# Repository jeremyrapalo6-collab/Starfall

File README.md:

# Starfall

Starfall is my first hardware project. I wanted to make a macropad because it seemed cool, and I chose to use my favorite colors, black and purple, along with my group name, **LTC**. This was a cool but long project, and I learned a lot while making it.

## What it is

Starfall is a 9-key macropad with a rotary encoder and a small OLED display. I designed it around a Seeed Studio XIAO RP2040 and made a custom PCB and case for it.

The macropad has three modes:

- **Everyday** - shortcuts for normal computer use
- **Gaming** - keys for games
- **Coding** - shortcuts for VS Code and Python

The bottom-right key changes between the three modes, and the OLED shows which mode is active.

## Design

The Celestial case pairs a black shell with purple side trusses, stars, a crescent and a bold slanted LTC logo. It has a stepped OLED surround and a recessed USB-C opening. Keycap symbols are illustrative; the preview includes the printable Starfall star knob.

## Hardware

- Seeed Studio XIAO RP2040
- 9 MX-compatible switches
- 9 1N4148 diodes
- 0.91-inch SSD1306 I2C OLED
- EC11 rotary encoder
- Custom 2-layer PCB
- Custom 3D-printed case
- 9 keycaps
- M3 screws and heat-set inserts

## Firmware

The firmware uses **KMK / CircuitPython**.

The three layers are:

### Everyday
Copy, paste, cut, undo, redo, select all, screenshot, media play/pause, and mode change.

### Gaming
A set of gaming keys plus the mode-change key.

### Coding
VS Code shortcuts such as run, debug, format, comment, terminal, split editor, command palette, quick open, and mode change.

## PCB

### Schematic

### PCB layout

### Front 3D view

### Back 3D view

### Gerber check

## Case

The current case is **Starfall Celestial** (114.4 x 116 x 22.9 mm including side trusses).

- Black: `production/Top.STEP` and `production/Bottom.STEP`.
- Purple: `production/Middle_Purple.STEP` and `production/Purple_Inlays_Print_Layout.STEP` (one set of accents).
- Matching STL files are provided. `Purple_Inlays.STEP` is the same accents in assembled positions: do not print both accent files.
- [Fully assembled STEP](CAD/Starfall_Fully_Assembled.STEP) and [colored GLB](CAD/Starfall_Fully_Assembled_Colored.glb).
- [Design changes and physical fit checks](DESIGN_NOTES.md) and [assembly instructions](CAD/MECHANICAL_NOTES.md).

The L has been shifted 0.35 mm right. The taller bottom retains M3x16 screws with recessed insert seats. The PCB layout is unchanged. Print the switch/insert coupons and check your actual cable before a full case: CAD checks do not guarantee physical fit. All files in production are current. The case PNGs and older assembly filenames are synchronized to the latest Celestial case; PCB screenshots describe the unchanged PCB.

Automated CAD results: [mechanical](production/MECHANICAL_VALIDATION.json), [exports](production/EXPORT_VALIDATION.json), [structural intersections](production/STRUCTURAL_COLLISIONS.json).

### Current case views

These views are rendered from the current assembly. Keycaps and legends are illustrative accessories; the knob matches the printable files. See [asset descriptions](assets/SCREENSHOTS.md).

[Download the complete printer ZIP (case + knob + samples)](production/Starfall-Complete-Printer-Pack.zip).

### Printable Starfall encoder knob

[Download the knob print pack](production/knob/Starfall-Knob-Print-Pack.zip) or browse [individual STL/STEP files and instructions](production/knob/README.md).

Print `Knob_Black.stl` in black and `Knob_Star_Purple.stl` in purple. Test `Dshaft_sample_6p2mm.stl` on the actual encoder first. The 6.1 and 6.3 mm samples provide fit alternatives; change the knob bore if needed before printing. Modeled clearances pass, but physical shaft fit and push travel require testing. Full-case previews and assembled STEP/GLB files now include this printable star knob.

## Bill of Materials

| Item | Qty | Part / Specification | Notes |
| --- | ---: | --- | --- |
| Microcontroller | 1 | Seeed Studio XIAO RP2040 | Hackpad MCU |
| Mechanical switch | 9 | MX-compatible PCB-mount switch | 1u switches |
| Diode | 9 | 1N4148 DO-35 through-hole | One per key |
| Rotary encoder | 1 | EC11E, 20 mm D-shaft | Encoder input |
| OLED | 1 | 0.91 in 128x32 SSD1306 I2C | 4-pin module |
| Keycap | 9 | 1u MX keycaps | 9 total |
| Encoder knob | 1 | D-shaft knob sized for EC11E | Knob for encoder |
| M3 screw | 4 | M3 x 16 mm | Deeper bottom; checked head envelope is diameter 5.5 x height 3 mm |
| Heat-set insert | 4 | M3 x 5 x 4 mm insert | 4.7 x 4.1 mm pocket below a 5.8 mm installation well |
| PCB | 1 | Starfall 2-layer PCB, 84.89 x 96.94 mm | Gerbers in `production/` |
| Case: black | 1 set | `Top.STEP` + `Bottom.STEP` | 3D printed |
| Case: purple | 1 set | `Middle_Purple.STEP` + `Purple_Inlays.STEP` | 3D printed accents |

The full BOM with source/reference links is also available in [`BOM.csv`](BOM.csv).

## Files

- `PCB/` - KiCad schematic, PCB, and project files
- `CAD/` - case, assemblies, and full-color GLB preview
- `production/` - final STEP/STL case parts, Gerbers, print-ready check, and `main.py`
- `Firmware/` - KMK firmware source
- `assets/` - project screenshots and graphics
- `tools/` - reproducible final-case generator
- `BOM.csv` - bill of materials with reference links

## What I learned

This was my first project, so I learned a lot about KiCad, schematics, PCB routing, key matrices, diodes, 3D models, case design, Gerbers, and firmware. It took a while, but seeing the whole project come together was worth it.

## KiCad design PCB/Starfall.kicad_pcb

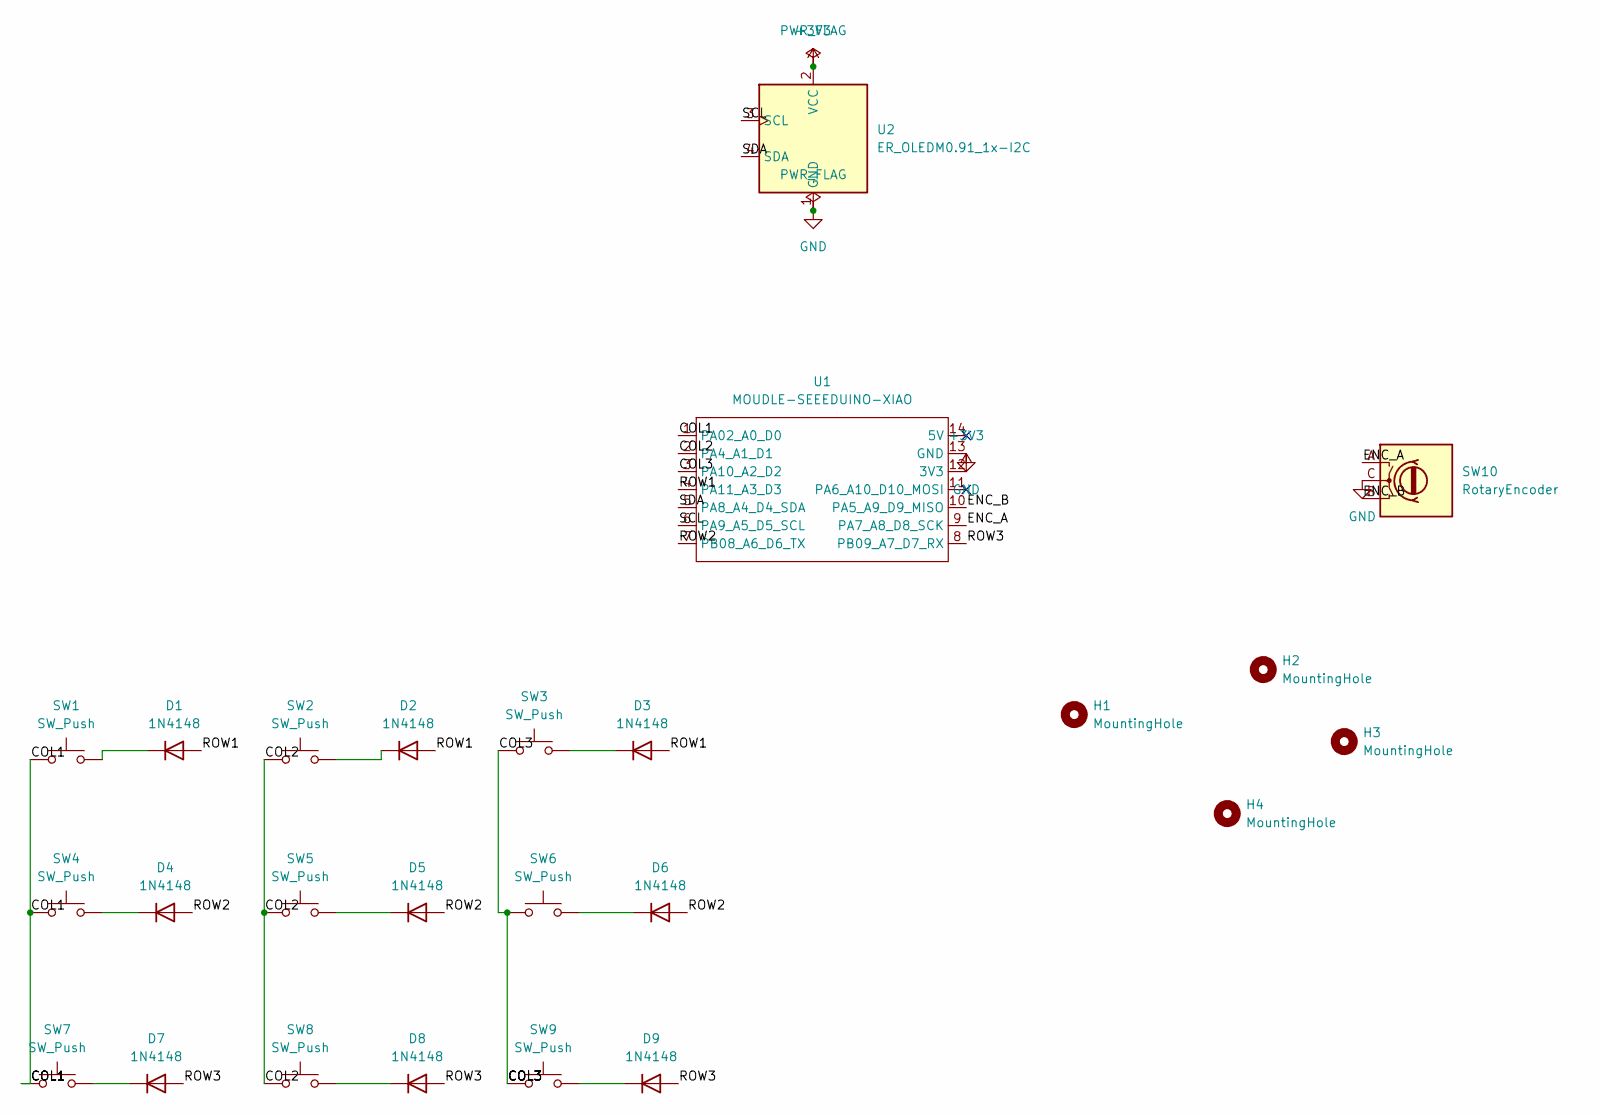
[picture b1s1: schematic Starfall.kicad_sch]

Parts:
D1, D2, D3, D4, D5, D6, D7, D8, D9: 1N4148; D_DO-35_SOD27_P10.16mm_Horizontal
H1, H2, H3, H4: MountingHole; MountingHole_3.2mm_M3
SW1, SW2, SW3, SW4, SW5, SW6, SW7, SW8, SW9: SW_Push; SW_Cherry_MX_1.00u_PCB
SW10: RotaryEncoder; RotaryEncoder_Alps_EC11E-Switch_Vertical_H20mm
U1: MOUDLE-SEEEDUINO-XIAO; XIAO-Generic-Hybrid-14P-2.54-21X17.8MM
U2: ER_OLEDM0.91_1x-I2C; SSD1306-0.91-OLED-4pin-128x32

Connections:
+3V3: U1.12 (3V3), U2.2 (VCC)
/COL1: SW1.1, SW4.1, SW7.1, U1.1 (PA02_A0_D0)
/COL2: SW2.1, SW5.1, SW8.1, U1.2 (PA4_A1_D1)
/COL3: SW3.1, SW6.1, SW9.1, U1.3 (PA10_A2_D2)
/ENC_A: SW10.A, U1.9 (PA7_A8_D8_SCK)
/ENC_B: SW10.B, U1.10 (PA5_A9_D9_MISO)
/ROW1: D1.2 (A), D2.2 (A), D3.2 (A), U1.4 (PA11_A3_D3)
/ROW2: D4.2 (A), D5.2 (A), D6.2 (A), U1.7 (PB08_A6_D6_TX)
/ROW3: D7.2 (A), D8.2 (A), D9.2 (A), U1.8 (PB09_A7_D7_RX)
/SCL: U1.6 (PA9_A5_D5_SCL), U2.3 (SCL)
/SDA: U1.5 (PA8_A4_D4_SDA), U2.4 (SDA)
GND: SW10.C, U1.13 (GND), U2.1 (GND)
unnamed: D1.1 (K), SW1.2
unnamed: D2.1 (K), SW2.2
unnamed: D3.1 (K), SW3.2
unnamed: D4.1 (K), SW4.2
unnamed: D5.1 (K), SW5.2
unnamed: D6.1 (K), SW6.2
unnamed: D7.1 (K), SW7.2
unnamed: D8.1 (K), SW8.2
unnamed: D9.1 (K), SW9.2

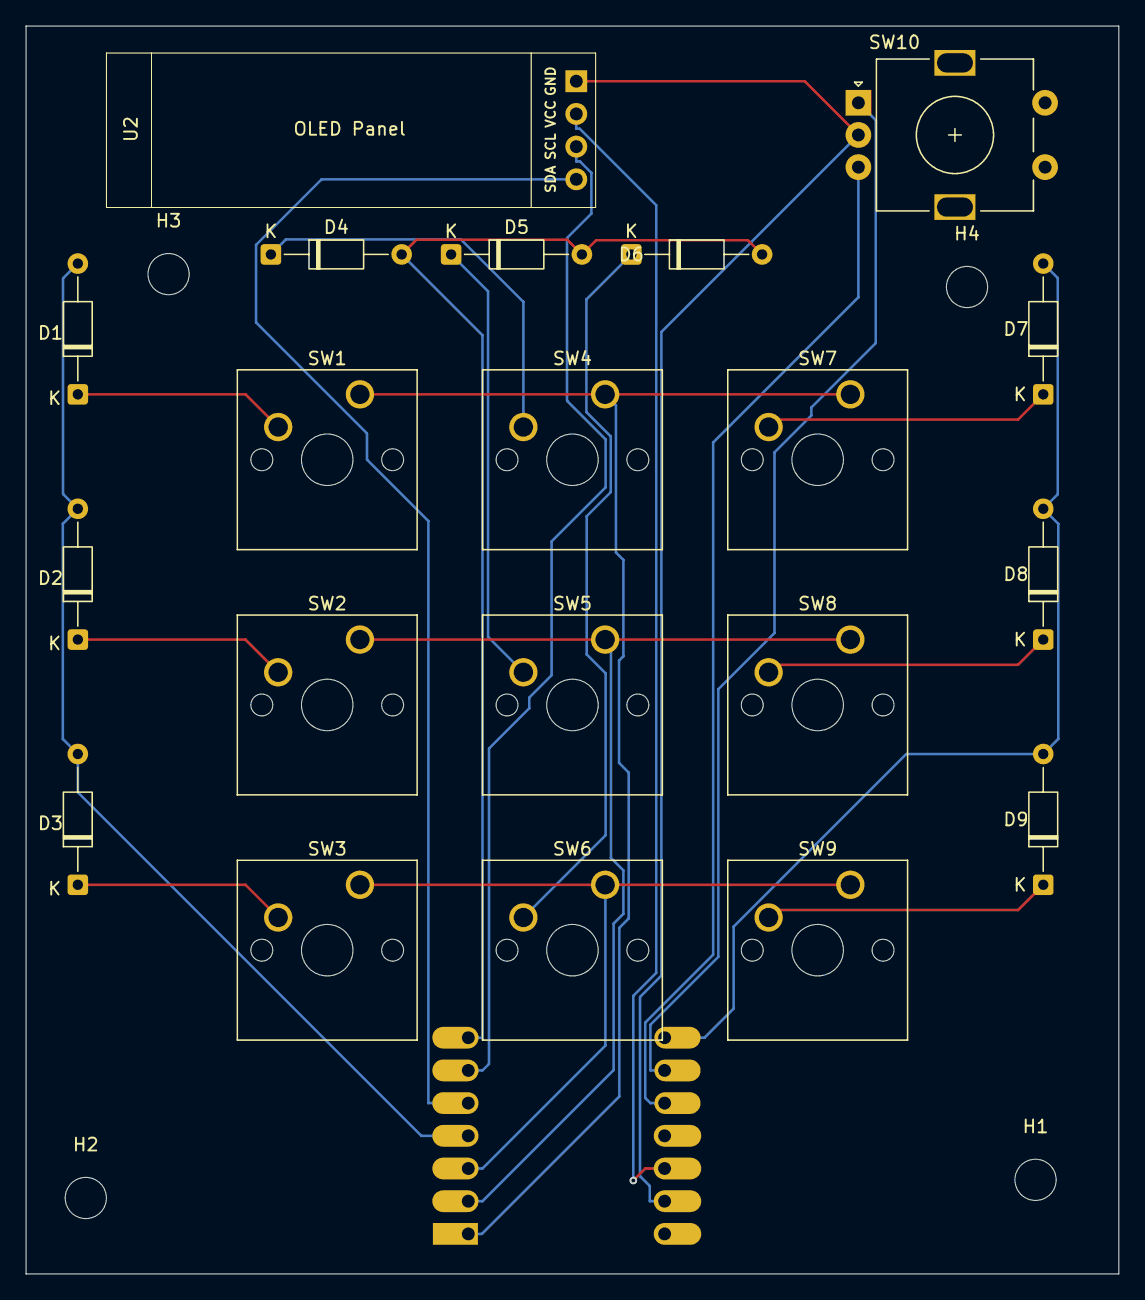
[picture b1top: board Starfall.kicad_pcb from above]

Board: 2 copper layers, 84.9 x 96.9 mm, 25 parts (1 on the bottom side), 21 nets.
